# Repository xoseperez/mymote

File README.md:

View this project on [CADLAB.io](https://cadlab.io/node/891). 

# mymote

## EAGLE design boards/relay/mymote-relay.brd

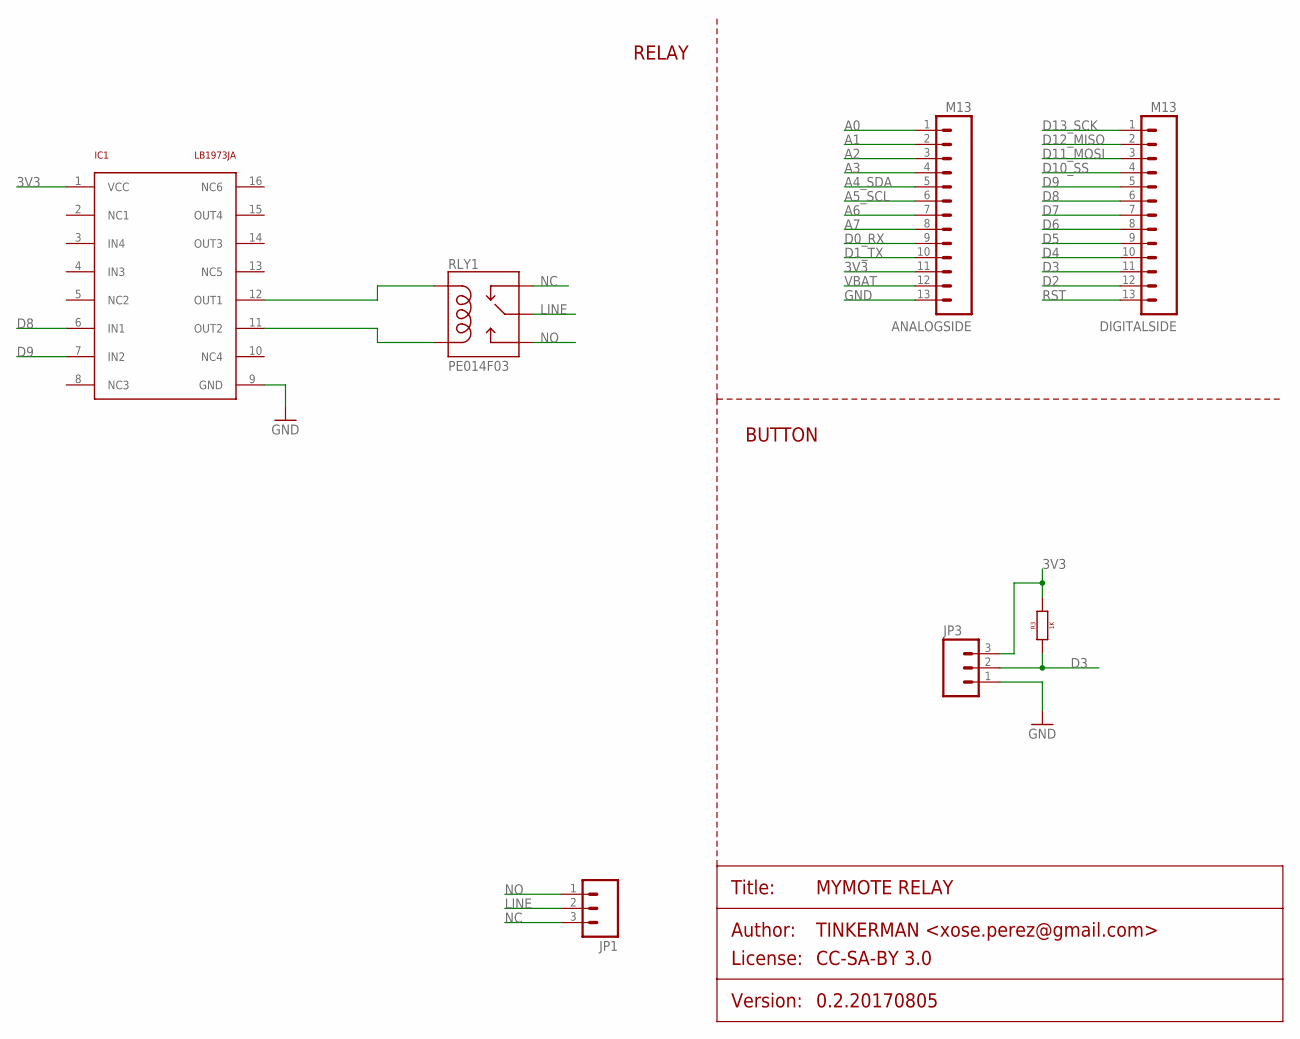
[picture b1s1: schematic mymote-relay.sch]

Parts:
ANALOGSIDE: M13; 1X13_NO_SILK
DIGITALSIDE: M13; 1X13_NO_SILK
IC1: LB1973JA; SSOP16
JP1: M03200MIL; SCREWTERMINAL-200MIL-3
JP3: M03JST-PTH-VERT; JST-3-PTH-VERT
R3: 1K; 0805
RLY1: PE014F03; PE014F0XX

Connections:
3V3: ANALOGSIDE.11, IC1.1 (VCC), JP3.3, R3.2
A0: ANALOGSIDE.1
A1: ANALOGSIDE.2
A2: ANALOGSIDE.3
A3: ANALOGSIDE.4
A4_SDA: ANALOGSIDE.5
A5_SCL: ANALOGSIDE.6
A6: ANALOGSIDE.7
A7: ANALOGSIDE.8
D0_RX: ANALOGSIDE.9
D1_TX: ANALOGSIDE.10
D2: DIGITALSIDE.12
D3: DIGITALSIDE.11, JP3.2, R3.1
D4: DIGITALSIDE.10
D5: DIGITALSIDE.9
D6: DIGITALSIDE.8
D7: DIGITALSIDE.7
D8: DIGITALSIDE.6, IC1.6 (IN1)
D9: DIGITALSIDE.5, IC1.7 (IN2)
D10_SS: DIGITALSIDE.4
D11_MOSI: DIGITALSIDE.3
D12_MISO: DIGITALSIDE.2
D13_SCK: DIGITALSIDE.1
GND: ANALOGSIDE.13, IC1.9 (GND), JP3.1
LINE: JP1.2, RLY1.COMMON (MAIN)
unnamed: IC1.12 (OUT1), RLY1.COIL1
unnamed: IC1.11 (OUT2), RLY1.COIL2
NC: JP1.3, RLY1.CLOSED (NC)
NO: JP1.1, RLY1.OPEN (NO)
RST: DIGITALSIDE.13
VBAT: ANALOGSIDE.12

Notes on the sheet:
RELAY
BUTTON

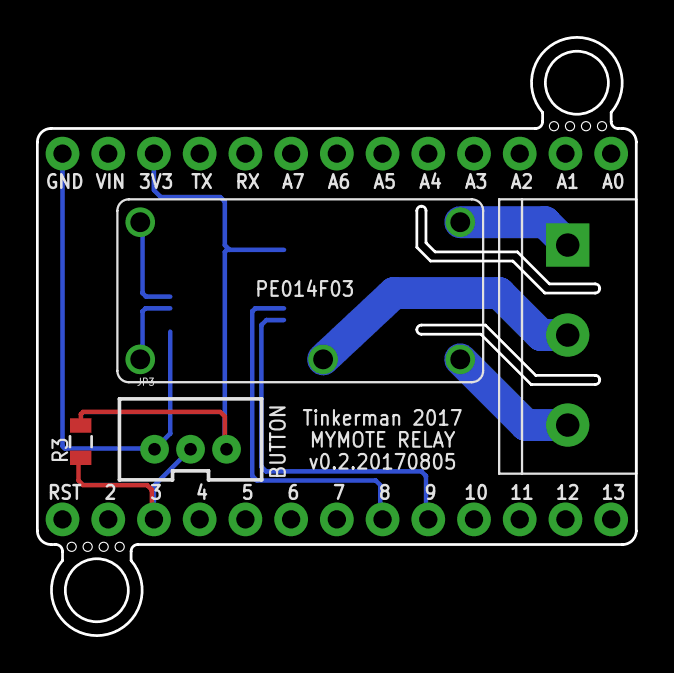
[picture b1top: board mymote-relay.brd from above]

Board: 2 copper layers, 33.3 x 33.2 mm, 7 parts (1 on the bottom side), 10 nets.

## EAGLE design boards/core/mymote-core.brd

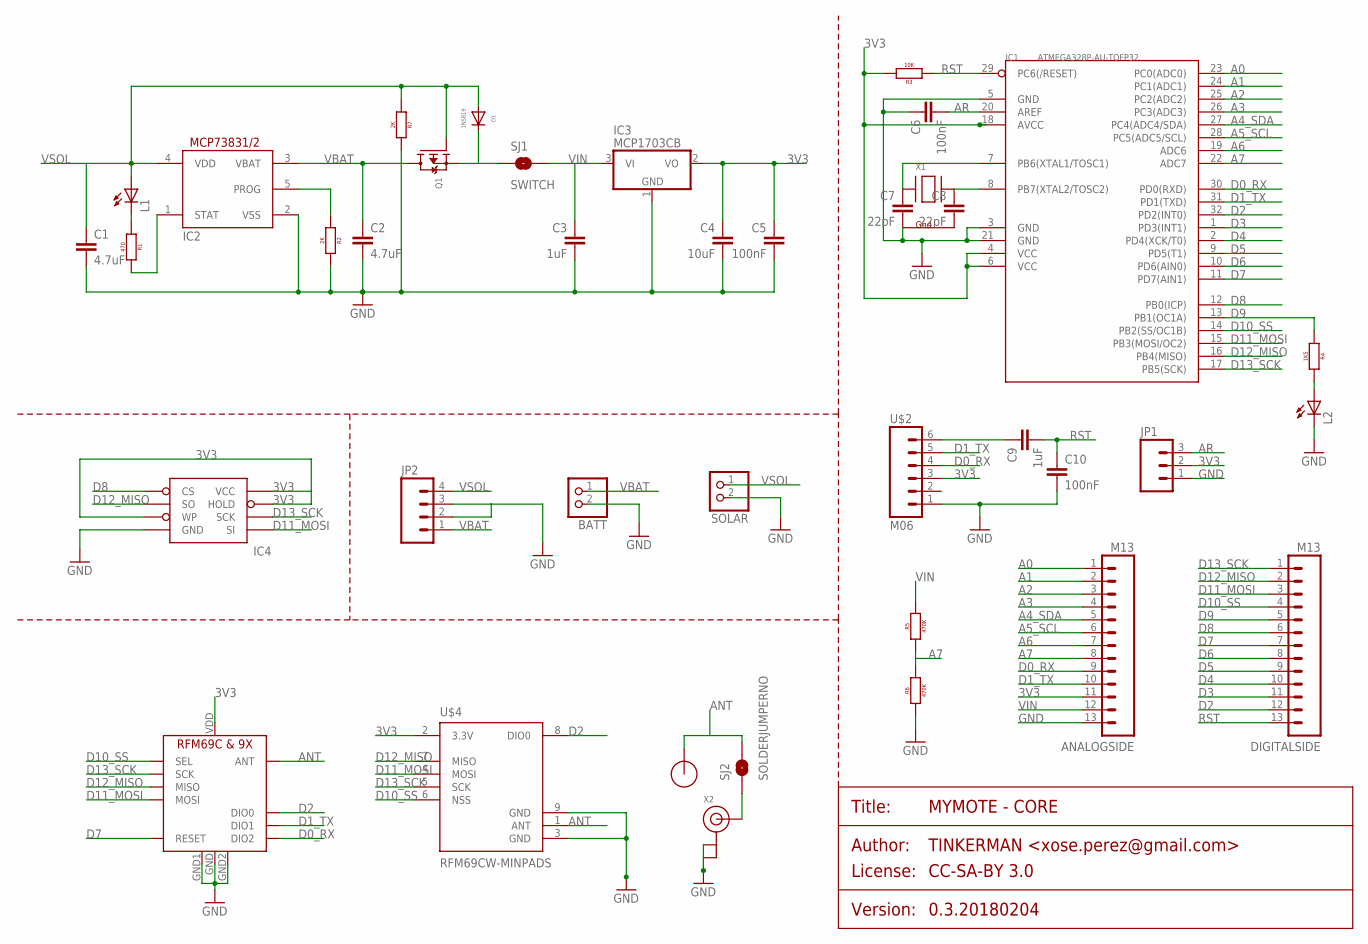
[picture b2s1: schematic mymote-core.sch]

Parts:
ANALOGSIDE: M13; 1X13_NO_SILK
BATT: JST_2PIN-SMT-RA; JST-PH-2-SMT-RA
C1, C2: 4.7uF; 0805
C3, C9: 1uF; 0805
C4: 10uF; 0805
C5, C6, C10: 100nF; 0805
C7, C8: 22pF; 0805
D1: 1N5819; 0805_DIODE
DIGITALSIDE: M13; 1X13_NO_SILK
IC1: ATMEGA328P-AU-TQFP32; TQFP32-0.8-7X7MM
IC2: MCP73831/OT; SOT23-5L
IC3: MCP1703CB; SOT23
IC4: AT25F512BWIDE_5.3MM; SO08WIDE
JP1: M03PTH; 1X03
JP2: M04PTH; 1X04
L1, L2: LED_0805; 0805_DIODE
Q1: MOSFET-PWIDE; SOT23-WIDE
R1: 470; 0805
R2, R7: 2K; 0805
R3: 10K; 0805
R4: 1K5; 0805
R5, R6: 470K; 0805
SJ1: SWITCH; SJ_2S-TRACE-PTH
SJ2: SOLDERJUMPERNO; SJ_2S-NO
SOLAR: JST_2PIN-SMT-RA; JST-PH-2-SMT-RA
U$1: RFM12B_ANTENNA; RFM12B-ANTENNA
U$2: M06; 1X06_NO_SILK
U$3: RFM69HCW-RFM95; RFM69HCW-RFM95-MINPADS
U$4: RFM69CW-MINPADS
X1: XTAL-4-3225; NX3225
X2: ANTENNA_U.FL; U.FL

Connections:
3V3: ANALOGSIDE.11, C4.1, C5.1, IC1.4 (VCC), IC1.6 (VCC), IC1.18 (AVCC), IC3.2 (VO), IC4.3 (WP), IC4.7 (HOLD), IC4.8 (VCC), JP1.2, R3.2, U$2.3, U$3.VDD (VCC), U$4.2 (3.3V)
A0: ANALOGSIDE.1, IC1.23 (PC0(ADC0))
A1: ANALOGSIDE.2, IC1.24 (PC1(ADC1))
A2: ANALOGSIDE.3, IC1.25 (PC2(ADC2))
A3: ANALOGSIDE.4, IC1.26 (PC3(ADC3))
A4_SDA: ANALOGSIDE.5, IC1.27 (PC4(ADC4/SDA))
A5_SCL: ANALOGSIDE.6, IC1.28 (PC5(ADC5/SCL))
A6: ANALOGSIDE.7, IC1.19 (ADC6)
A7: ANALOGSIDE.8, IC1.22 (ADC7), R5.1, R6.2
ANT: SJ2.2, U$1.P$1, U$3.ANT, U$4.1 (ANT)
AR: C6.2, IC1.20 (AREF), JP1.3
D0_RX: ANALOGSIDE.9, IC1.30 (PD0(RXD)), U$2.4, U$3.DIO2
D1_TX: ANALOGSIDE.10, IC1.31 (PD1(TXD)), U$2.5, U$3.DIO1
D2: DIGITALSIDE.12, IC1.32 (PD2(INT0)), U$3.DIO0, U$4.8 (DIO0)
D3: DIGITALSIDE.11, IC1.1 (PD3(INT1))
D4: DIGITALSIDE.10, IC1.2 (PD4(XCK/T0))
D5: DIGITALSIDE.9, IC1.9 (PD5(T1))
D6: DIGITALSIDE.8, IC1.10 (PD6(AIN0))
D7: DIGITALSIDE.7, IC1.11 (PD7(AIN1)), U$3.RESET
D8: DIGITALSIDE.6, IC1.12 (PB0(ICP)), IC4.1 (CS)
D9: DIGITALSIDE.5, IC1.13 (PB1(OC1A)), R4.1
D10_SS: DIGITALSIDE.4, IC1.14 (PB2(SS/OC1B)), U$3.NSS (SEL), U$4.6 (NSS)
D11_MOSI: DIGITALSIDE.3, IC1.15 (PB3(MOSI/OC2)), IC4.5 (SI), U$3.MOSI, U$4.4 (MOSI)
D12_MISO: DIGITALSIDE.2, IC1.16 (PB4(MISO)), IC4.2 (SO), U$3.MISO, U$4.7 (MISO)
D13_SCK: DIGITALSIDE.1, IC1.17 (PB5(SCK)), IC4.6 (SCK), U$3.SCK, U$4.5 (SCK)
GND: ANALOGSIDE.13, BATT.2 (1), C1.2, C2.2, C3.2, C4.2, C5.2, C6.1, C7.2, C10.2, IC1.3 (GND), IC1.5 (GND), IC1.21 (GND), IC2.2 (VSS), IC3.1 (GND), IC4.4 (GND), JP1.1, JP2.2, JP2.3, L2.C, R2.2, R6.1, R7.2, SOLAR.2 (1), U$2.1, U$3.GND, U$3.GND1, U$3.GND2, U$4.3 (GND), U$4.9 (GND), X1.4 (G1), X2.1 (GND), X2.2 (GND)
unnamed: L2.A, R4.2
unnamed: L1.C, R1.1
unnamed: IC2.5 (PROG), R2.1
unnamed: IC2.1 (STAT), R1.2
unnamed: C7.1, IC1.7 (PB6(XTAL1/TOSC1)), X1.1 (X1)
unnamed: C9.1, U$2.6
unnamed: SJ2.1, X2.3 (SIGNAL)
unnamed: D1.C, Q1.2 (S), SJ1.1
unnamed: C8.1, IC1.8 (PB7(XTAL2/TOSC2)), X1.3 (X2)
unnamed: C8.2, X1.2 (G2)
RST: C9.2, C10.1, DIGITALSIDE.13, IC1.29 (PC6(/RESET)), R3.1
VBAT: BATT.1 (2), C2.1, IC2.3 (VBAT), JP2.1, Q1.3 (D)
VIN: ANALOGSIDE.12, C3.1, IC3.3 (VI), R5.2, SJ1.2
VSOL: C1.1, D1.A, IC2.4 (VDD), JP2.4, L1.A, Q1.1 (G), R7.1, SOLAR.1 (2)

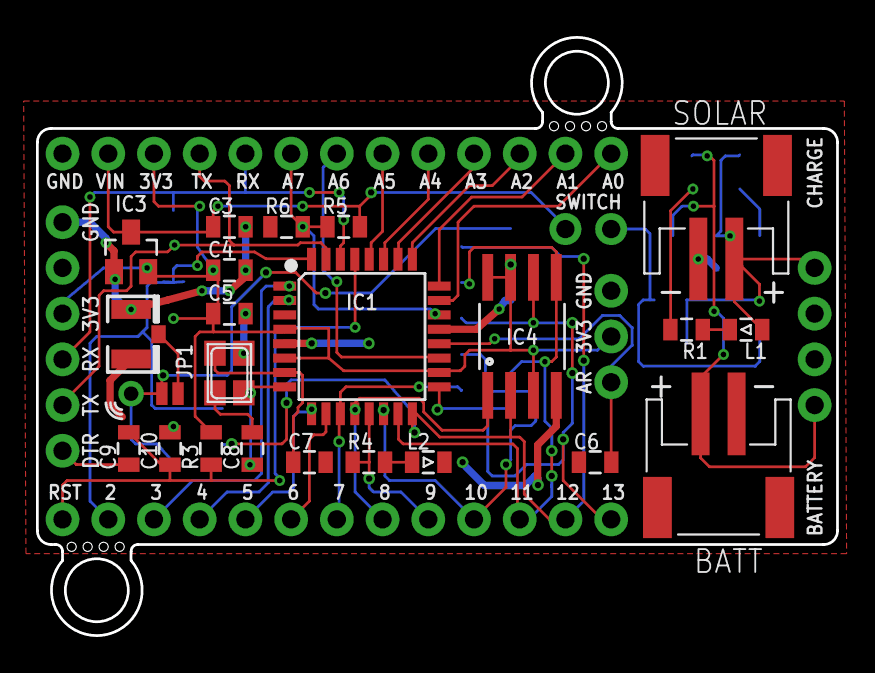
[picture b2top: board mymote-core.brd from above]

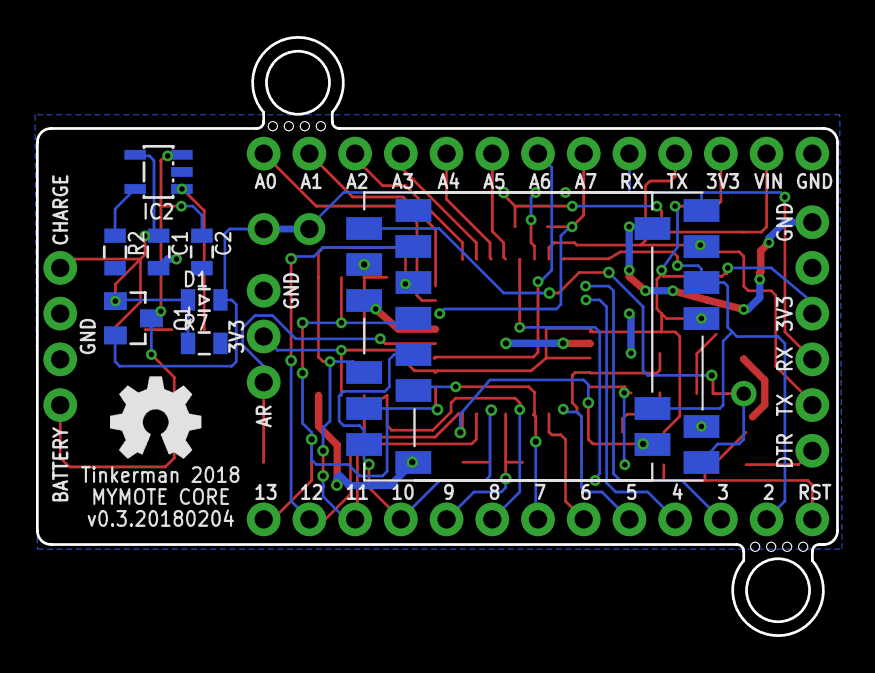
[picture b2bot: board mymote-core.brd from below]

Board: 2 copper layers, 44.5 x 33.2 mm, 39 parts (9 on the bottom side), 40 nets.

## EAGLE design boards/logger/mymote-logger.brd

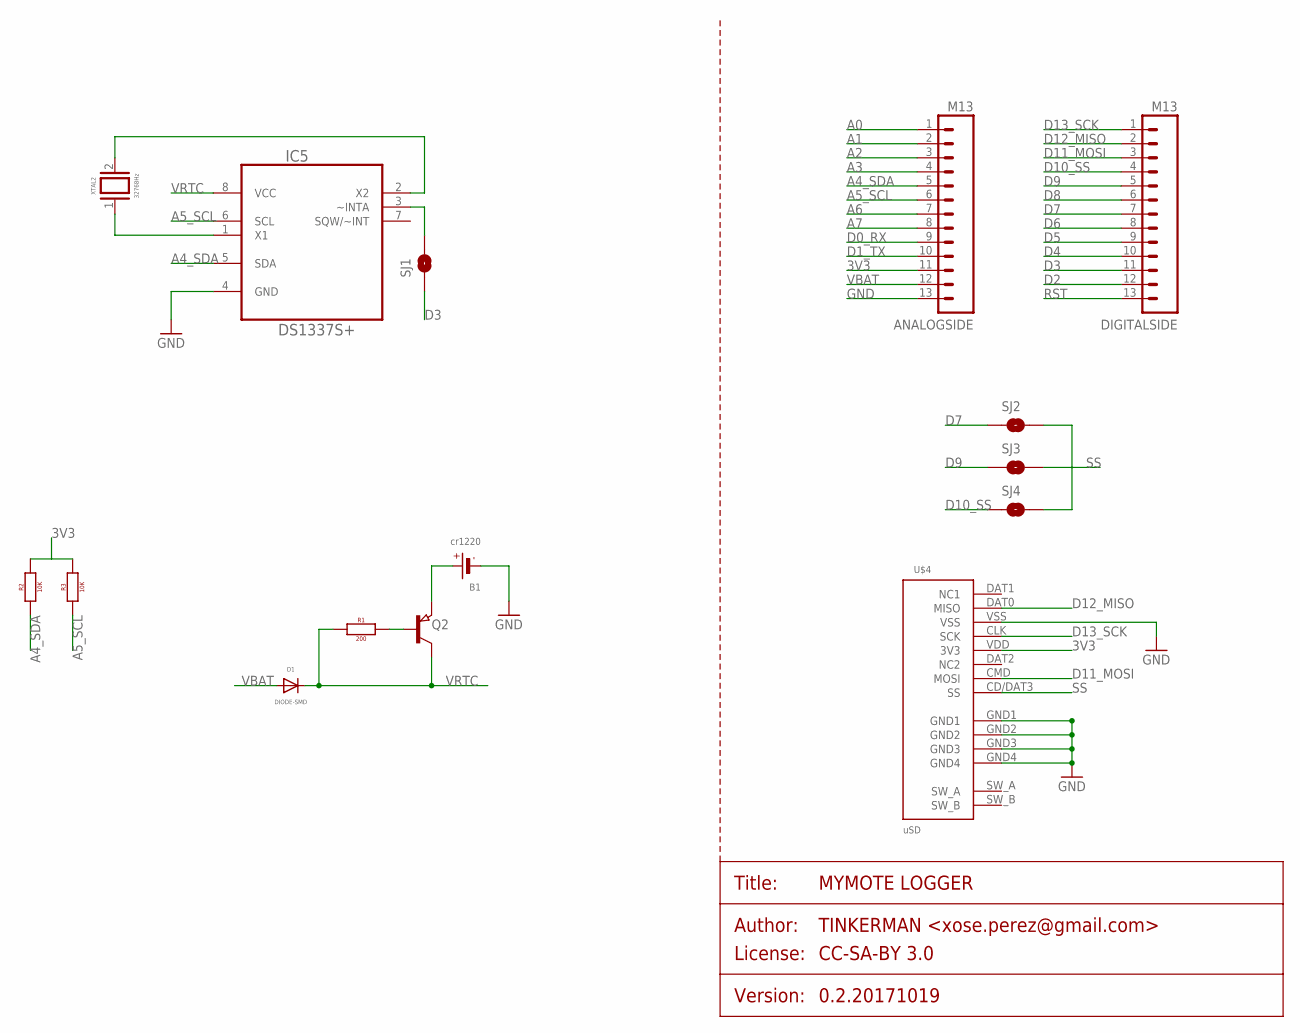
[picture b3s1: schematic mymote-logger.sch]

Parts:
ANALOGSIDE: M13; 1X13_NO_SILK
B1: cr1220; CR1220-2
D1: DIODE-SMD; 0805_DIODE
DIGITALSIDE: M13; 1X13_NO_SILK
IC5: DS1337S+; SOIC127P600X175-8N
Q2: PNP-TRANSISTOR_SOT23; SOT23
R1: 200; 0805
R2, R3: 10K; 0805
SJ1, SJ2, SJ3, SJ4: SOLDERJUMPERNO; SJ_2S-NO
U$4: uSD; DM3D
XTAL2: 32768Hz; TC38H

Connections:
3V3: ANALOGSIDE.11, R2.2, R3.2, U$4.VDD (3V3)
A0: ANALOGSIDE.1
A1: ANALOGSIDE.2
A2: ANALOGSIDE.3
A3: ANALOGSIDE.4
A4_SDA: ANALOGSIDE.5, IC5.5 (SDA), R2.1
A5_SCL: ANALOGSIDE.6, IC5.6 (SCL), R3.1
A6: ANALOGSIDE.7
A7: ANALOGSIDE.8
D0_RX: ANALOGSIDE.9
D1_TX: ANALOGSIDE.10
D2: DIGITALSIDE.12
D3: DIGITALSIDE.11, SJ1.1
D4: DIGITALSIDE.10
D5: DIGITALSIDE.9
D6: DIGITALSIDE.8
D7: DIGITALSIDE.7, SJ2.1
D8: DIGITALSIDE.6
D9: DIGITALSIDE.5, SJ3.1
D10_SS: DIGITALSIDE.4, SJ4.1
D11_MOSI: DIGITALSIDE.3, U$4.CMD (MOSI)
D12_MISO: DIGITALSIDE.2, U$4.DAT0 (MISO)
D13_SCK: DIGITALSIDE.1, U$4.CLK (SCK)
GND: ANALOGSIDE.13, B1.-, IC5.4 (GND), U$4.GND1, U$4.GND2, U$4.GND3, U$4.GND4, U$4.VSS
unnamed: IC5.1 (X1), XTAL2.1
unnamed: IC5.2 (X2), XTAL2.2
unnamed: Q2.1 (B), R1.2
unnamed: B1.+, Q2.2 (E)
unnamed: IC5.3 (~INTA), SJ1.2
RST: DIGITALSIDE.13
SS: SJ2.2, SJ3.2, SJ4.2, U$4.CD/DAT3 (SS)
VBAT: ANALOGSIDE.12, D1.A
VRTC: D1.C, IC5.8 (VCC), Q2.3 (C), R1.1

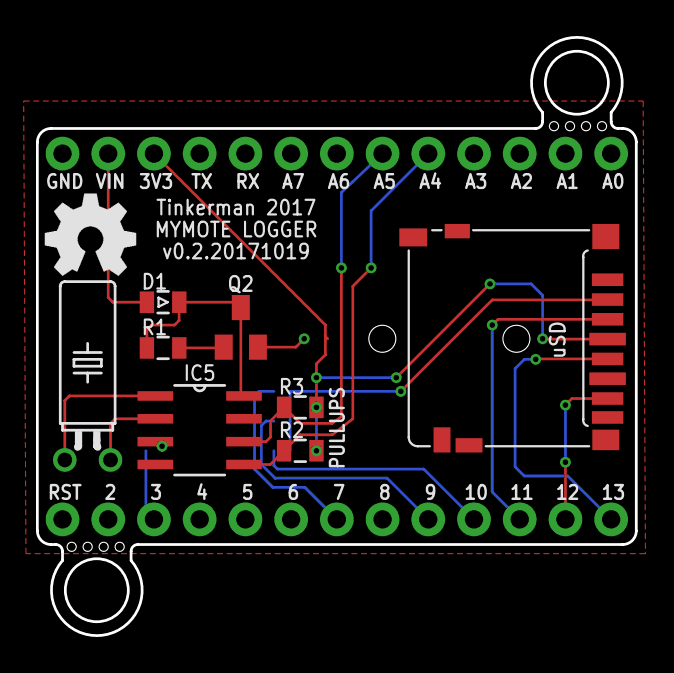
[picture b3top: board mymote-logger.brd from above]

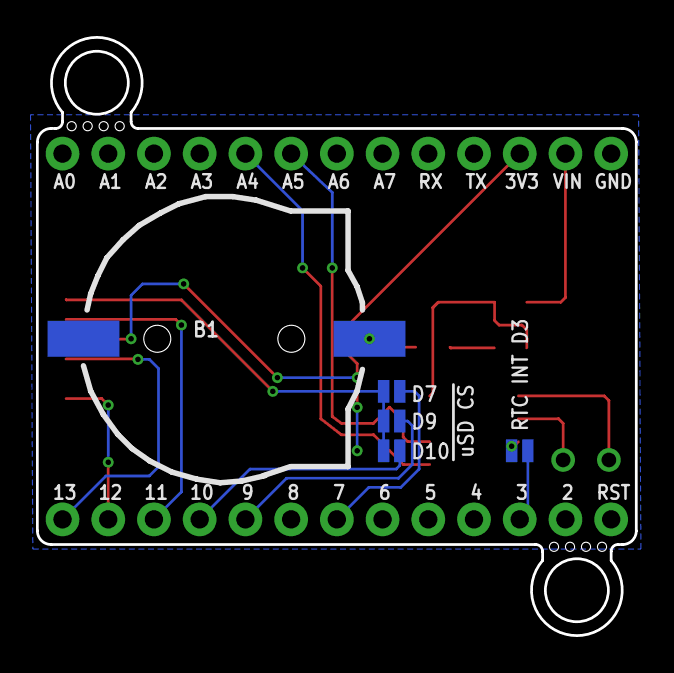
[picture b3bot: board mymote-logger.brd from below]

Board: 2 copper layers, 33.3 x 33.2 mm, 15 parts (5 on the bottom side), 19 nets.

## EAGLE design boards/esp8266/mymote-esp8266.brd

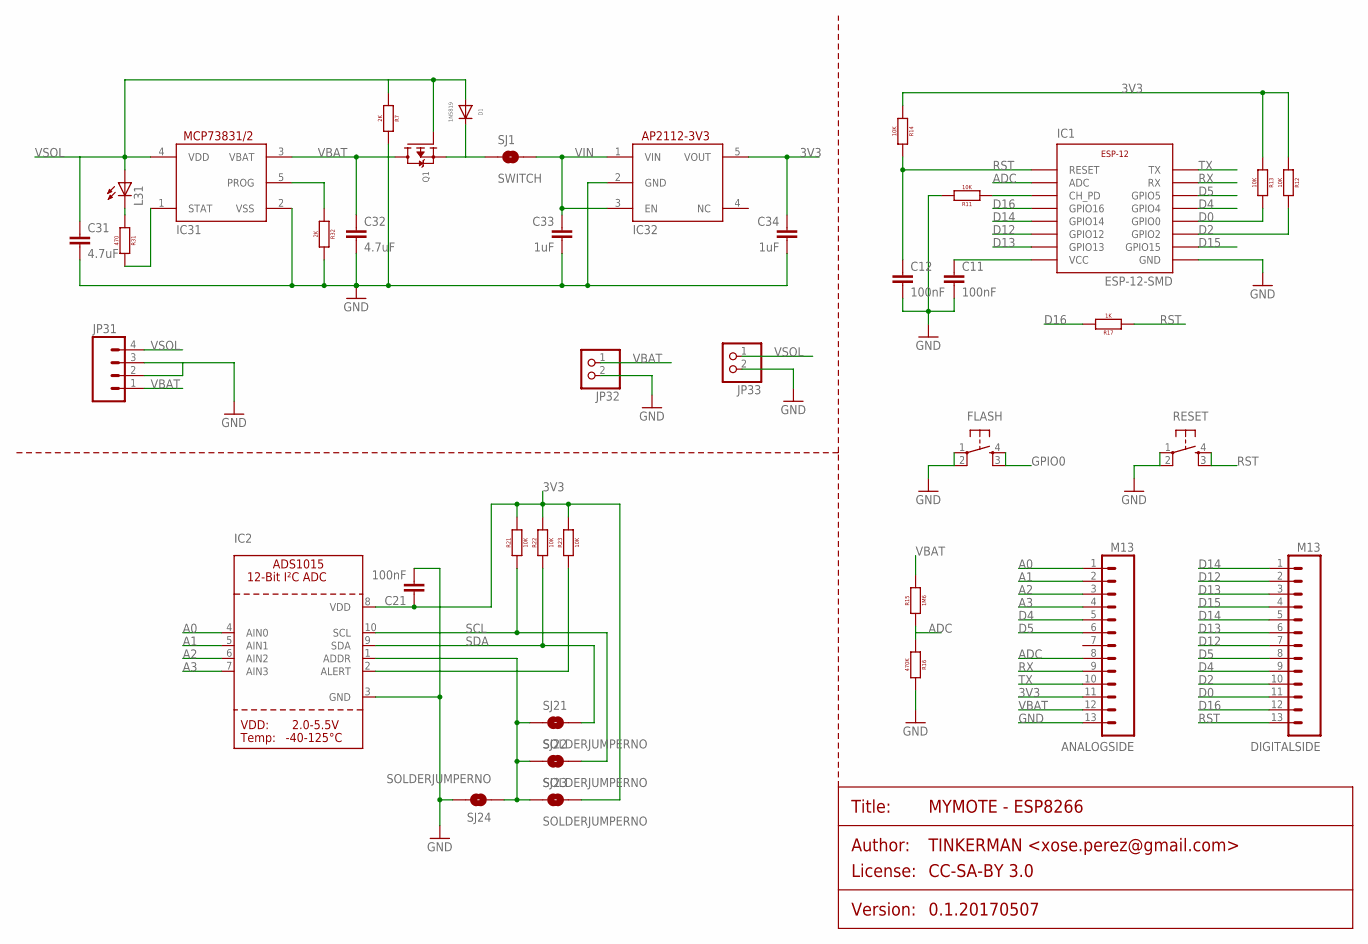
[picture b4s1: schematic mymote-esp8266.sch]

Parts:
ANALOGSIDE: M13; 1X13_NO_SILK
C11, C12, C21: 100nF; 0805
C31, C32: 4.7uF; 0805
C33, C34: 1uF; 0805
D1: 1N5819; 0805_DIODE
DIGITALSIDE: M13; 1X13_NO_SILK
FLASH: TACTILE_BUTTON_SMD; TACTILE-BUTTON-SMD
IC1: ESP-12-SMD
IC2: ADC_ADS1015; MSOP10
IC31: MCP73831/OT; SOT23-5L
IC32: AP2112-3V3; SOT23-5L
JP31: M04PTH; 1X04
JP32, JP33: JST_2PIN-SMT-RA; JST-PH-2-SMT-RA
L31: LED_0805; 0805_DIODE
Q1: MOSFET-PWIDE; SOT23-WIDE
R7, R32: 2K; 0805
R11, R12, R13, R14, R21, R22, R23: 10K; 0805
R15: 1M6; 0805
R16: 470K; 0805
R17: 1K; 0805
R31: 470; 0805
RESET: TACTILE_BUTTON_SMD; TACTILE-BUTTON-SMD
SJ1: SWITCH; SJ_2S-TRACE-PTH
SJ21, SJ22, SJ23, SJ24: SOLDERJUMPERNO; SJ_2S-NO

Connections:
3V3: ANALOGSIDE.11, C11.1, C21.1, C34.1, IC1.VCC, IC2.8 (VDD), IC32.5 (VOUT), R12.1, R13.1, R14.1, R21.2, R22.2, R23.2, SJ23.2
A0: ANALOGSIDE.1, IC2.4 (AIN0)
A1: ANALOGSIDE.2, IC2.5 (AIN1)
A2: ANALOGSIDE.3, IC2.6 (AIN2)
A3: ANALOGSIDE.4, IC2.7 (AIN3)
ADC: ANALOGSIDE.8, IC1.ADC, R15.1, R16.1
D0: DIGITALSIDE.11, IC1.GPIO0, R13.2
D2: DIGITALSIDE.10, IC1.GPIO2, R12.2
D4: ANALOGSIDE.5, DIGITALSIDE.9, IC1.GPIO4
D5: ANALOGSIDE.6, DIGITALSIDE.8, IC1.GPIO5
D12: DIGITALSIDE.2, DIGITALSIDE.7, IC1.GPIO12
D13: DIGITALSIDE.3, DIGITALSIDE.6, IC1.GPIO13
D14: DIGITALSIDE.1, DIGITALSIDE.5, IC1.GPIO14
D15: DIGITALSIDE.4, IC1.GPIO15
D16: DIGITALSIDE.12, IC1.GPIO16, R17.2
GND: ANALOGSIDE.13, C11.2, C12.2, C21.2, C31.2, C32.2, C33.2, C34.2, FLASH.1 (SWA1), FLASH.2 (SWB1), IC1.GND, IC2.3 (GND), IC31.2 (VSS), IC32.2 (GND), JP31.2, JP31.3, JP32.2 (1), JP33.2 (1), R7.2, R11.2, R16.2, R32.2, RESET.1 (SWA1), RESET.2 (SWB1), SJ24.2
GPIO0: FLASH.3 (SWB2), FLASH.4 (SWA2)
unnamed: IC1.CH_PD, R11.1
unnamed: L31.C, R31.1
unnamed: IC31.5 (PROG), R32.1
unnamed: IC31.1 (STAT), R31.2
unnamed: D1.C, Q1.2 (S), SJ1.1
unnamed: IC2.2 (ALERT), R23.1
unnamed: IC2.1 (ADDR), SJ21.1, SJ22.1, SJ23.1, SJ24.1
RST: C12.1, DIGITALSIDE.13, IC1.RESET, R14.2, R17.1, RESET.3 (SWB2), RESET.4 (SWA2)
RX: ANALOGSIDE.9, IC1.RX
SCL: IC2.10 (SCL), R21.1, SJ22.2
SDA: IC2.9 (SDA), R22.1, SJ21.2
TX: ANALOGSIDE.10, IC1.TX
VBAT: ANALOGSIDE.12, C32.1, IC31.3 (VBAT), JP31.1, JP32.1 (2), Q1.3 (D), R15.2
VIN: C33.1, IC32.1 (VIN), IC32.3 (EN), SJ1.2
VSOL: C31.1, D1.A, IC31.4 (VDD), JP31.4, JP33.1 (2), L31.A, Q1.1 (G), R7.1

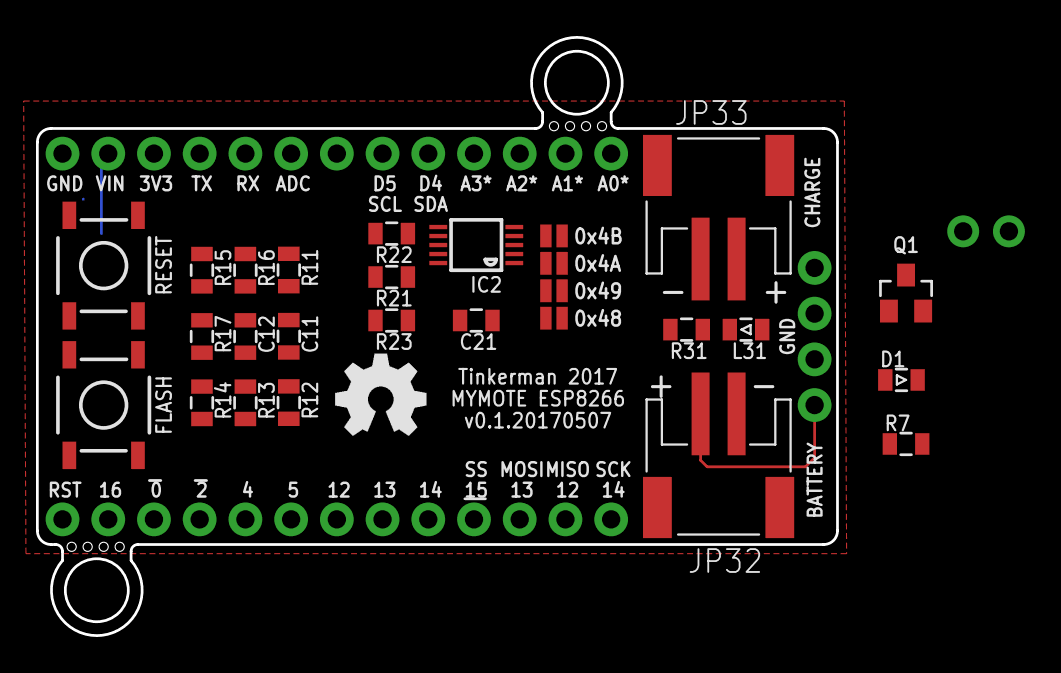
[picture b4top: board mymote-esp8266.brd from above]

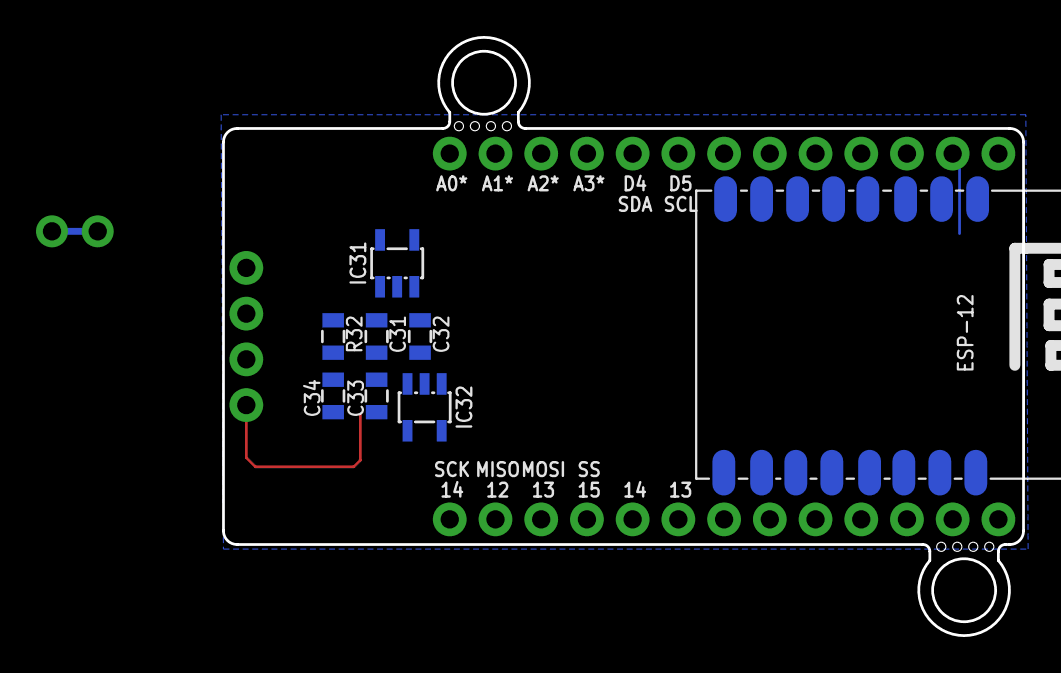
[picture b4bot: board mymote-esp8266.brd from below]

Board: 2 copper layers, 44.5 x 33.2 mm, 39 parts (8 on the bottom side), 32 nets.

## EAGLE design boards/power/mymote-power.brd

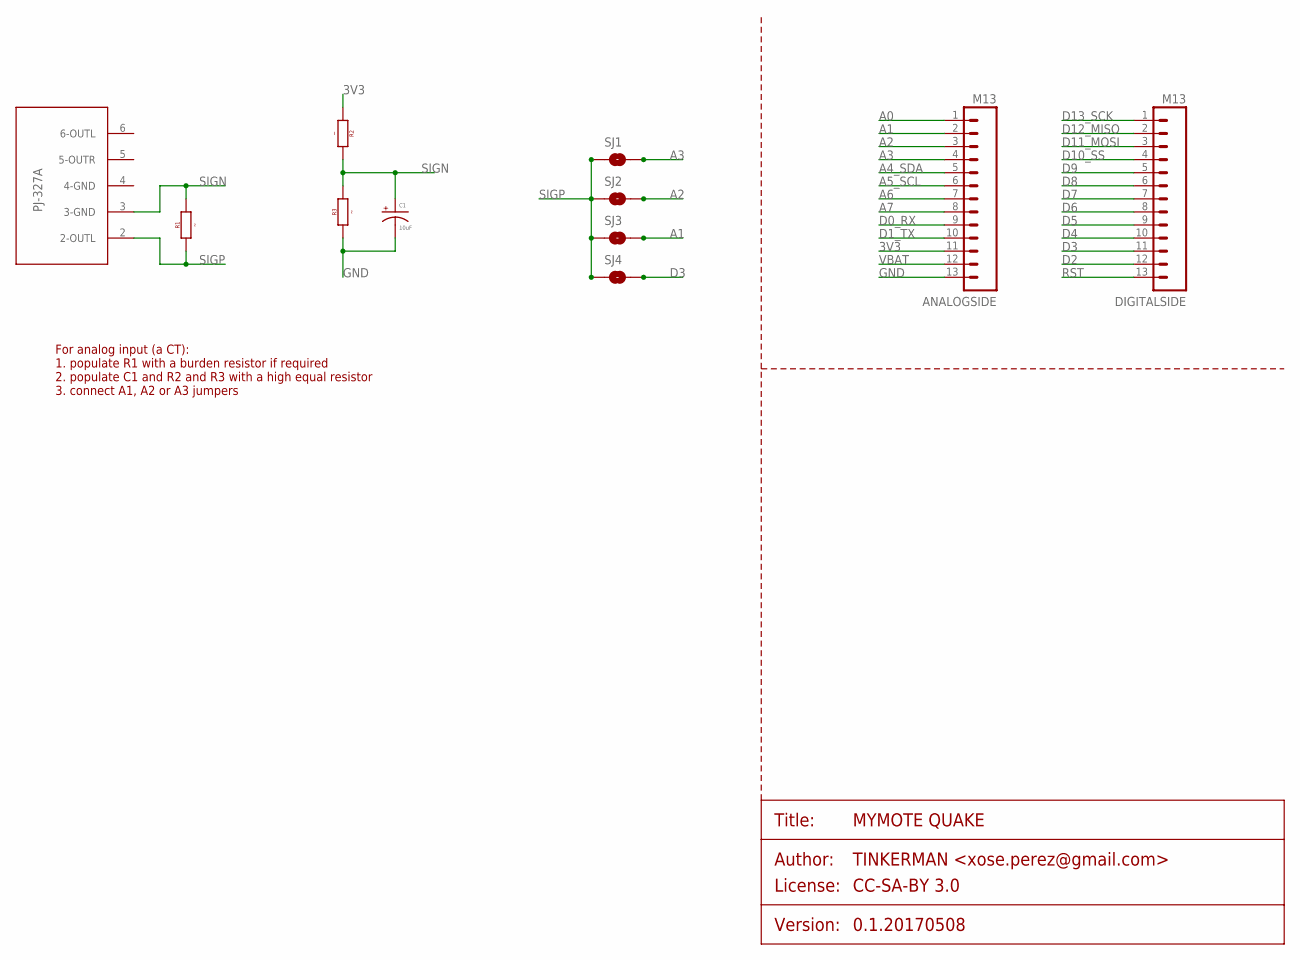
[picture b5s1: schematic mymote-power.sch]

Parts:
ANALOGSIDE: M13; 1X13_NO_SILK
C1: 10uF; PANASONIC_C
CURR1: PJ-327A
DIGITALSIDE: M13; 1X13_NO_SILK
R1, R2, R3: 0805
SJ1, SJ2, SJ3, SJ4: SOLDERJUMPERNO; SJ_2S-NO

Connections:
3V3: ANALOGSIDE.11, R2.1
A0: ANALOGSIDE.1
A1: ANALOGSIDE.2, SJ3.2
A2: ANALOGSIDE.3, SJ2.2
A3: ANALOGSIDE.4, SJ1.2
A4_SDA: ANALOGSIDE.5
A5_SCL: ANALOGSIDE.6
A6: ANALOGSIDE.7
A7: ANALOGSIDE.8
D0_RX: ANALOGSIDE.9
D1_TX: ANALOGSIDE.10
D2: DIGITALSIDE.12
D3: DIGITALSIDE.11, SJ4.2
D4: DIGITALSIDE.10
D5: DIGITALSIDE.9
D6: DIGITALSIDE.8
D7: DIGITALSIDE.7
D8: DIGITALSIDE.6
D9: DIGITALSIDE.5
D10_SS: DIGITALSIDE.4
D11_MOSI: DIGITALSIDE.3
D12_MISO: DIGITALSIDE.2
D13_SCK: DIGITALSIDE.1
GND: ANALOGSIDE.13, C1.-, R3.1
RST: DIGITALSIDE.13
SIGN: C1.+, CURR1.3 (3-GND), R1.2, R2.2, R3.2
SIGP: CURR1.2 (2-OUTL), R1.1, SJ1.1, SJ2.1, SJ3.1, SJ4.1
VBAT: ANALOGSIDE.12

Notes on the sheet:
For analog input (a CT): 1. populate R1 with a burden resistor if required 2. populate C1 and R2 and R3 with a high equal resistor 3. connect A1, A2 or A3 jumpers

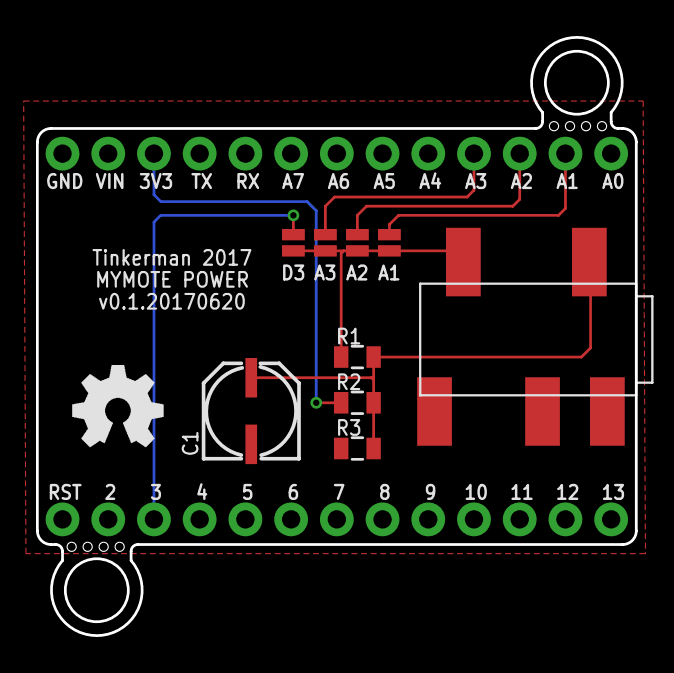
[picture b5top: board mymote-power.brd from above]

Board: 2 copper layers, 33.3 x 33.2 mm, 11 parts (0 on the bottom side), 8 nets.

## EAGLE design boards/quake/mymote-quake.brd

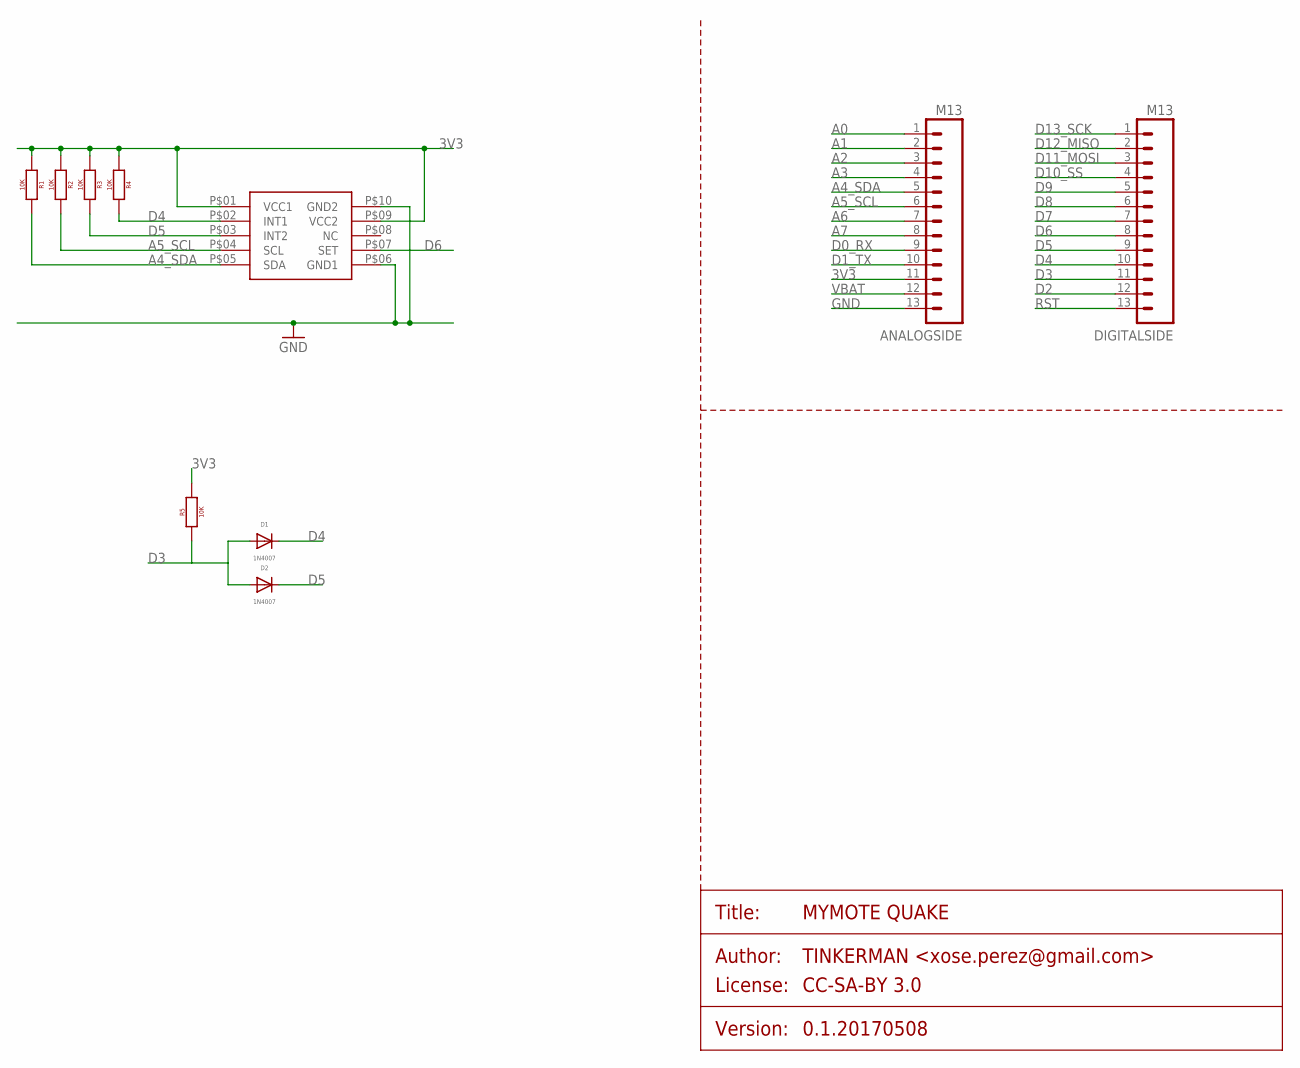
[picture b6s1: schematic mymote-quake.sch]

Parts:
ANALOGSIDE: M13; 1X13_NO_SILK
D1, D2: 1N4007; 0805_DIODE
DIGITALSIDE: M13; 1X13_NO_SILK
R1, R2, R3, R4, R5: 10K; 0805
U$1: D7S-A0001

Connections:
3V3: ANALOGSIDE.11, R1.1, R2.1, R3.1, R4.1, R5.2, U$1.P$01 (VCC1), U$1.P$09 (VCC2)
A0: ANALOGSIDE.1
A1: ANALOGSIDE.2
A2: ANALOGSIDE.3
A3: ANALOGSIDE.4
A4_SDA: ANALOGSIDE.5, R1.2, U$1.P$05 (SDA)
A5_SCL: ANALOGSIDE.6, R2.2, U$1.P$04 (SCL)
A6: ANALOGSIDE.7
A7: ANALOGSIDE.8
D0_RX: ANALOGSIDE.9
D1_TX: ANALOGSIDE.10
D2: DIGITALSIDE.12
D3: D1.A, D2.A, DIGITALSIDE.11, R5.1
D4: D1.C, DIGITALSIDE.10, R4.2, U$1.P$02 (INT1)
D5: D2.C, DIGITALSIDE.9, R3.2, U$1.P$03 (INT2)
D6: DIGITALSIDE.8, U$1.P$07 (SET)
D7: DIGITALSIDE.7
D8: DIGITALSIDE.6
D9: DIGITALSIDE.5
D10_SS: DIGITALSIDE.4
D11_MOSI: DIGITALSIDE.3
D12_MISO: DIGITALSIDE.2
D13_SCK: DIGITALSIDE.1
GND: ANALOGSIDE.13, U$1.P$06 (GND1), U$1.P$10 (GND2)
RST: DIGITALSIDE.13
VBAT: ANALOGSIDE.12

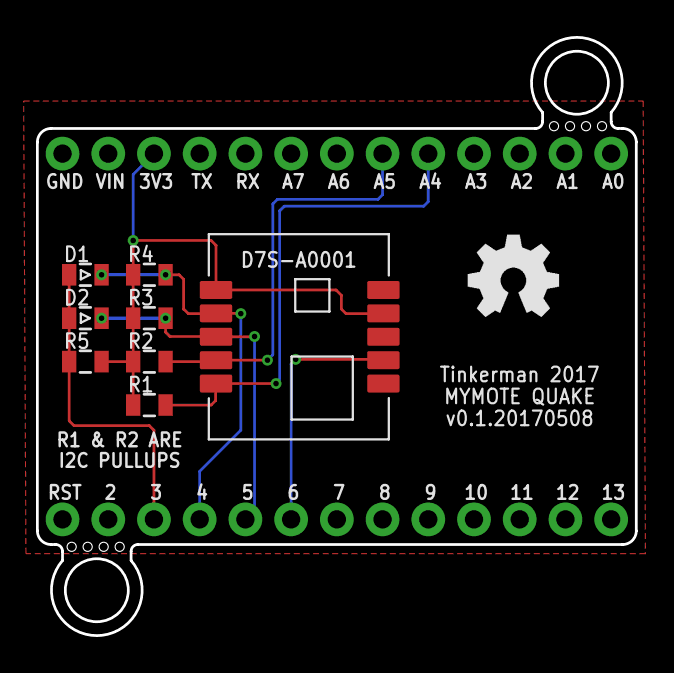
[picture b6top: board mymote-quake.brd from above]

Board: 2 copper layers, 33.3 x 33.2 mm, 10 parts (0 on the bottom side), 8 nets.

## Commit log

2017-07-05 Relay board and oter small changes
2018-04-16 Backlink to CADLAB.io has been added.

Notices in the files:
boards/core/mymote-core.sch:
PROJECT_LICENSE: CC-SA-BY 3.0
parts and their libraries:
SparkFun-Aesthetics: Licensing: Creative Commons ShareAlike 4.0 International - https://creativecommons.org/licenses/by-sa/4.0
microbuilder: This work is placed in the public domain, and may be freely used for commercial and non-commercial work with the following conditions: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
